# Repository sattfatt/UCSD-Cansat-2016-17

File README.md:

# UCSD-Cansat-2016-17
All code for CANSAT including ground station

# To-Do:

Tobin: create a function called release that turns a servo 90 degrees.

Angelica: create a function that ensbles a buzzer.

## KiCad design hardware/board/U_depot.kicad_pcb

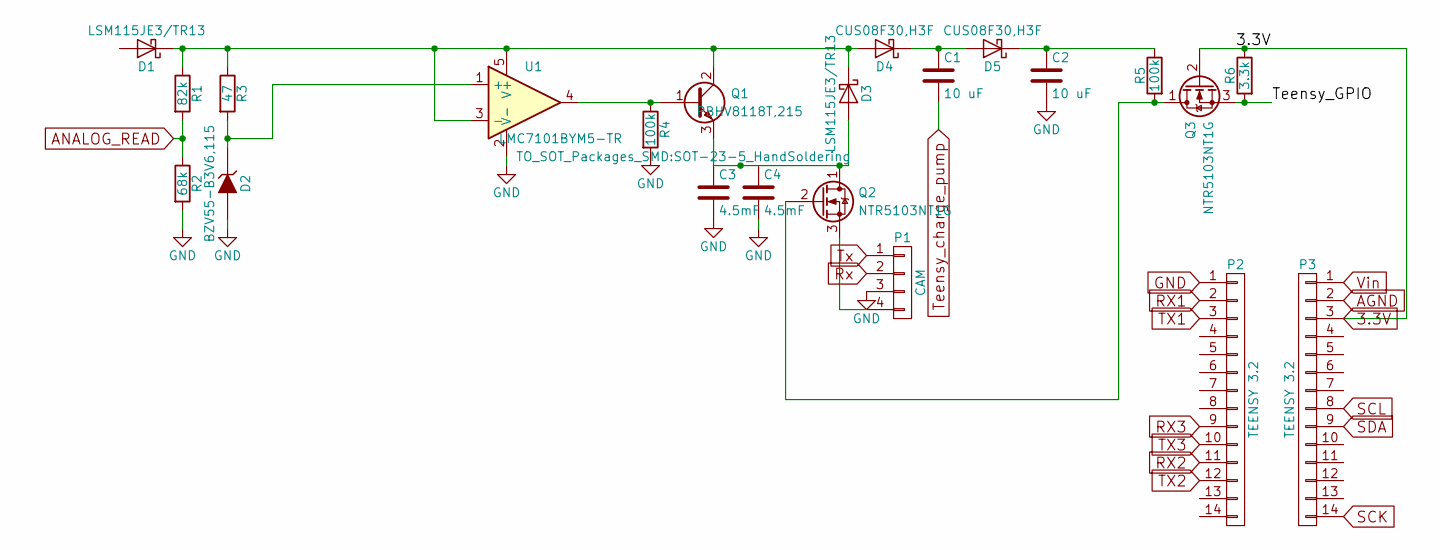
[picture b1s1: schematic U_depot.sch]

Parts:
C1, C2: 10 uF; CP_Radial_D5.0mm_P2.00mm
C3, C4: 4.5mF; CP_Radial_D18.0mm_P7.50mm
D1: LSM115JE3/TR13; D_SMB_Handsoldering
D2: BZV55-B3V6,115; D_SCD80_HandSoldering
D3: LSM115JE3/TR13; D_SMB_Handsoldering; Part Number LSM115JE3/TR13
D4: CUS08F30,H3F; D_SOD-323
D5: CUS08F30,H3F; D_SOD-323_HandSoldering
P1: CAM; Pin_Header_Angled_1x04_Pitch2.54mm
P2, P3: TEENSY 3.2; Pin_Header_Straight_1x14_Pitch2.54mm
Q1: PBHV8118T,215; SOT-23
Q2, Q3: NTR5103NT1G; SOT-23
R1: 82k; R_0603_HandSoldering
R2: 68k; R_0603_HandSoldering
R3: 47; R_0603_HandSoldering
R4, R5: 100k; R_0805_HandSoldering
R6: 3.3k; R_0805_HandSoldering
U1: LMC7101BYM5-TR; SOT-23-5_HandSoldering; Part Number LMC7101BYM5-TR

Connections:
3.3V: P3.3, Q3.2 (G), R6.1
/Teensy_GPIO: Q3.3 (S), R6.2
AGND: P3.2
ANALOG_READ: R1.2, R2.1
GND: C2.2, C3.2, C4.2, D2.2 (A), P1.3, P2.1, R2.2, R4.2, U1.2 (V-)
unnamed: C1.1, D4.1 (K), D5.2 (A)
unnamed: C2.1, D5.1 (K), R5.1
unnamed: C3.1, D3.2 (A), Q1.3 (E), Q2.1 (D)
unnamed: D1.1 (K), D3.1 (K), D4.2 (A), Q1.2 (C), R1.1, R3.1, U1.3 (-), U1.5 (V+)
unnamed: D2.1 (K), R3.2, U1.1 (+)
unnamed: P1.4, Q2.3 (S)
unnamed: Q1.1 (B), R4.1, U1.4
unnamed: Q2.2 (G), Q3.1 (D), R5.2
RX1: P2.2
RX2: P2.11
RX3: P2.9
Rx: P1.2
SCK: P3.14
SCL: P3.8
SDA: P3.9
TX1: P2.3
TX2: P2.12
TX3: P2.10
Teensy_charge_pump: C1.2
Tx: P1.1
Vin: P3.1

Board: 2 copper layers, 22 parts (0 on the bottom side), 12 nets, no tracks yet.

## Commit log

2016-06-28 New GCS using pyQT
2016-10-22 Added an empty LTSpice Simulation file for simulation the power system.
2016-10-22 This is the can code.
2016-10-22 this is the glider code
2016-10-22 added documentation for the voltage regulator on the Teensy
2016-10-22 Added components to the sim. Still need to added the voltage regulator.
2016-10-22 Added cannerdata.h struct created an instance in canner.ino globally
2016-10-26 GCS can now work on windows using top level workaround. Temporary fix.
2016-10-29 Organizational changes to gcs. Backend and Graphics have their own class with ui object passed in
2016-10-29 added symbol for voltage regulator
2016-10-29 updated schematic
2016-10-29 moved some stuff around for the sim
2016-10-29 made simulation portable (hopefully)
2016-10-29 moved stuff around again
2016-10-29 added diode model thingie
2016-10-29 added file for zener diode
2016-10-29 simulation is more complete
2016-10-29 latest update Winson made
2016-10-30 added ticks to 3d view
2016-10-30 Added some ticks and NSEW to 3d plot
2016-10-30 Recomitting
2016-11-05 sim runs now but is slow
2016-11-05 update sim
2016-11-05 this is the telemetry code
2016-11-05 added the giant diode in parallel to solar cell
2016-11-05 switched BJT to NMOS
2016-11-05 "This is canner logging code"
2016-11-05 tasks
2016-11-05 Minor changes
2016-11-05 Updated tasks to do
2016-11-12 sim works
2016-11-12 sim will test large transient loads
2016-11-12 added the zener diode schem
2016-11-12 sim with wrong reference
2016-11-12 replaced diodes with schottky diode, replaced the zener diode with a new zener diode
2016-11-12 the sim works, I think
2016-11-12 added schottky diodes
2016-11-12 i think i fixed what i messed up
2016-11-12 Added state detection framework and buzzer/release servo control. Also added relavent data to struct.
2016-11-14 Save Figure now actually can save the figure as jpg png or tif.
2016-11-20 Added full state detection
2017-01-21 Fixed compilation errors in canner.ino and made minor changes to cannerdata.h
2017-01-21 Starting point for glider code
2017-01-21 stuff
2017-01-21 stated project
2017-01-21 added some stuff
2017-01-21 Updated Glider Code
2017-01-28 glider
2017-02-11 deleted some random image file
2017-02-11 added some parts of the rtc and interrupt code
2017-02-11 kicad circuit almost done
2017-02-11 Added Arduino libraries needed for can and glider
2017-02-11 parts addded
2017-02-21 added cam code to glider
2017-02-25 reorganized send packet data
2017-02-25 updated logData
2017-02-25 finish with footprints
2017-02-25 started designing board
2017-02-25 added new header file, changed main file to test heading angle
2017-03-04 tried to add trace. TRIED.
2017-03-04 updated schottky diode footprint
